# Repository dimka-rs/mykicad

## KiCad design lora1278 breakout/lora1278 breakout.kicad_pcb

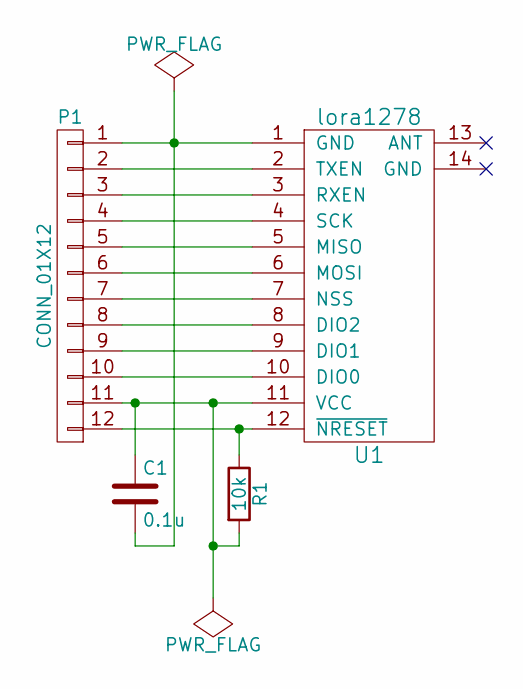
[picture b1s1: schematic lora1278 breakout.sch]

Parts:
C1: 0.1u; C_0805_HandSoldering
P1: CONN_01X12; Pin_Header_Straight_1x12
R1: 10k; R_0805_HandSoldering
U1: lora1278

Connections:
unnamed: C1.1, P1.11, R1.2, U1.11 (VCC)
unnamed: C1.2, P1.1, U1.1 (GND)
unnamed: P1.2, U1.2 (TXEN)
unnamed: P1.3, U1.3 (RXEN)
unnamed: P1.4, U1.4 (SCK)
unnamed: P1.5, U1.5 (MISO)
unnamed: P1.6, U1.6 (MOSI)
unnamed: P1.7, U1.7 (NSS)
unnamed: P1.8, U1.8 (DIO2)
unnamed: P1.9, U1.9 (DIO1)
unnamed: P1.10, U1.10 (DIO0)
unnamed: P1.12, R1.1, U1.12 (~NRESET)

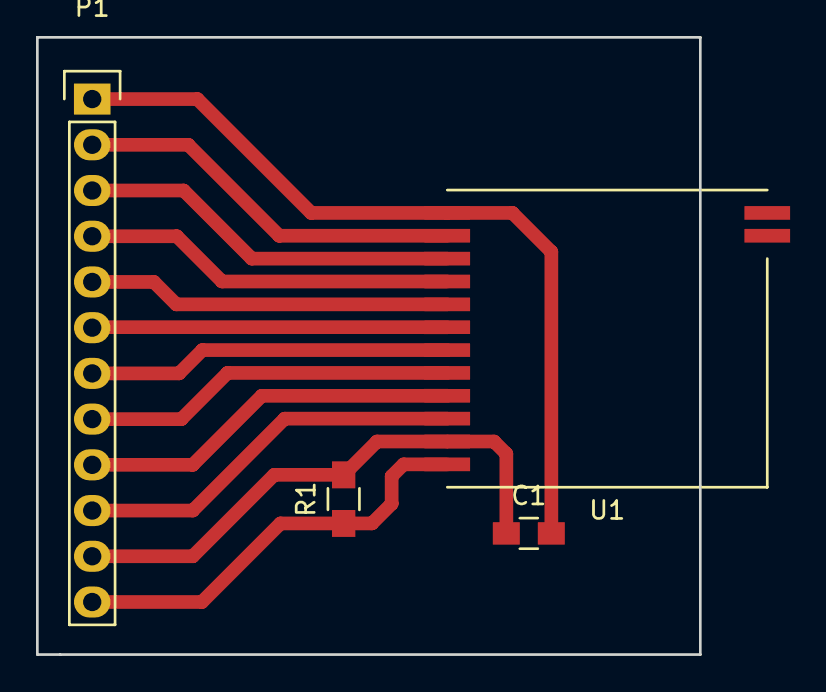
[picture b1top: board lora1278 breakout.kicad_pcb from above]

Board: 2 copper layers, 36.8 x 34.3 mm, 4 parts (0 on the bottom side), 12 nets.

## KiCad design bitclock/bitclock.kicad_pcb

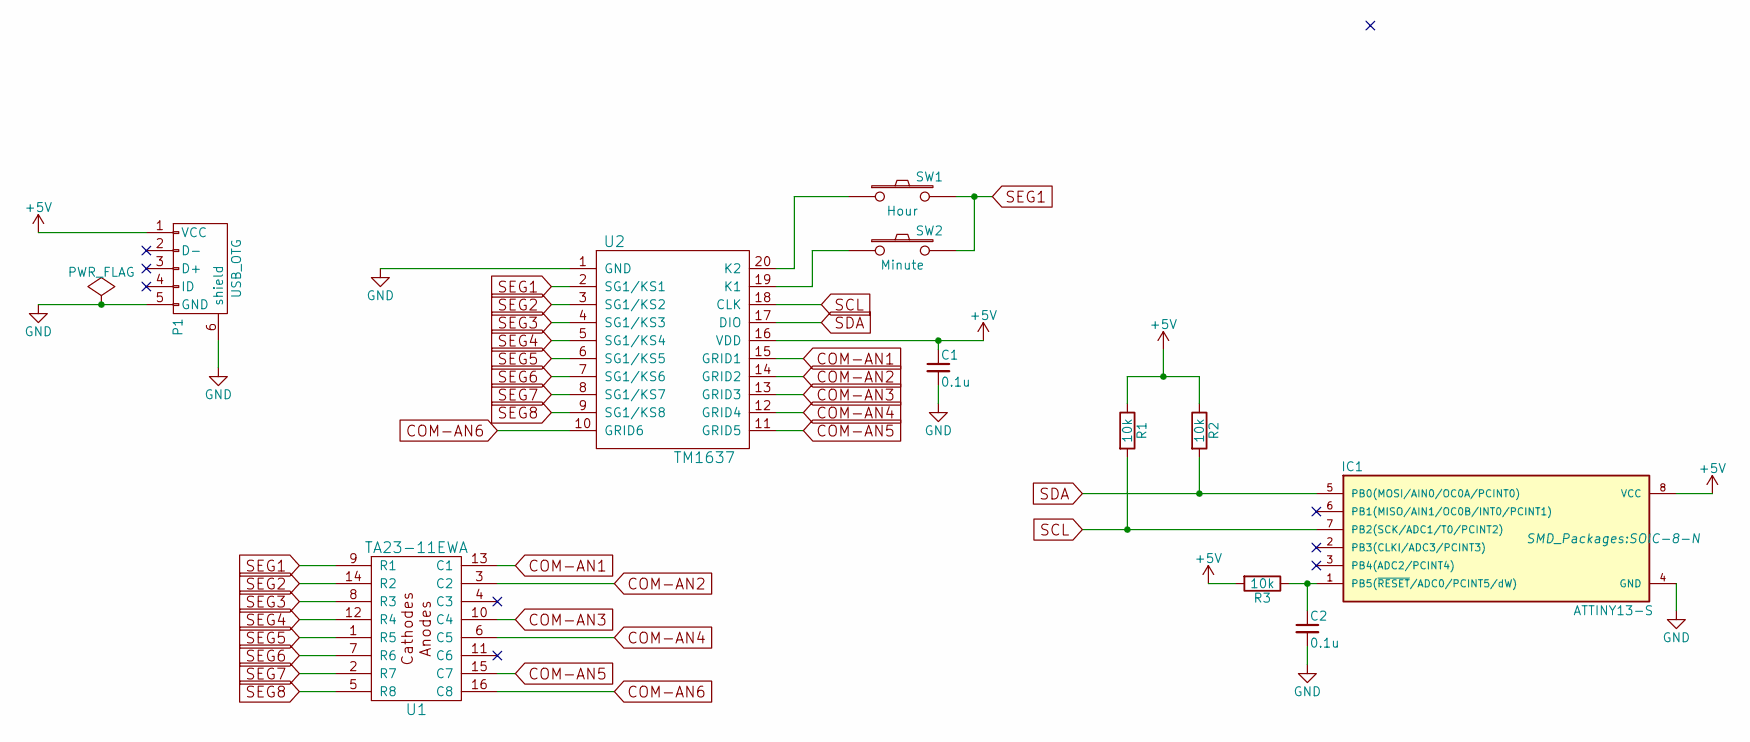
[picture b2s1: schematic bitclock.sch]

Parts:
C1, C2: 0.1u; C_0805_HandSoldering
IC1: ATTINY13-S; SOIC-8-N
P1: USB_OTG; USB_Mini-B
R1, R2, R3: 10k; R_0805_HandSoldering
SW1: Hour; SW_PUSH_SMALL
SW2: Minute; SW_PUSH_SMALL
U1: TA23-11EWA
U2: TM1637; SOIC-20_7.5x12.8mm_Pitch1.27mm

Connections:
+5V: C1.1, IC1.8 (VCC), P1.1 (VCC), R1.1, R2.1, R3.2, U2.16 (VDD)
COM-AN1: U1.13 (C1), U2.15 (GRID1)
COM-AN2: U1.3 (C2), U2.14 (GRID2)
COM-AN3: U1.10 (C4), U2.13 (GRID3)
COM-AN4: U1.6 (C5), U2.12 (GRID4)
COM-AN5: U1.15 (C7), U2.11 (GRID5)
COM-AN6: U1.16 (C8), U2.10 (GRID6)
GND: C1.2, C2.2, IC1.4 (GND), P1.5 (GND), P1.6 (shield), U2.1 (GND)
unnamed: C2.1, IC1.1 (PB5(~RESET~/ADC0/PCINT5/dW)), R3.1
unnamed: SW1.1, U2.20 (K2)
unnamed: SW2.1, U2.19 (K1)
SCL: IC1.7 (PB2(SCK/ADC1/T0/PCINT2)), R1.2, U2.18 (CLK)
SDA: IC1.5 (PB0(MOSI/AIN0/OC0A/PCINT0)), R2.2, U2.17 (DIO)
SEG1: SW1.2, SW2.2, U1.9 (R1), U2.2 (SG1/KS1)
SEG2: U1.14 (R2), U2.3 (SG1/KS2)
SEG3: U1.8 (R3), U2.4 (SG1/KS3)
SEG4: U1.12 (R4), U2.5 (SG1/KS4)
SEG5: U1.1 (R5), U2.6 (SG1/KS5)
SEG6: U1.7 (R6), U2.7 (SG1/KS6)
SEG7: U1.2 (R7), U2.8 (SG1/KS7)
SEG8: U1.5 (R8), U2.9 (SG1/KS8)

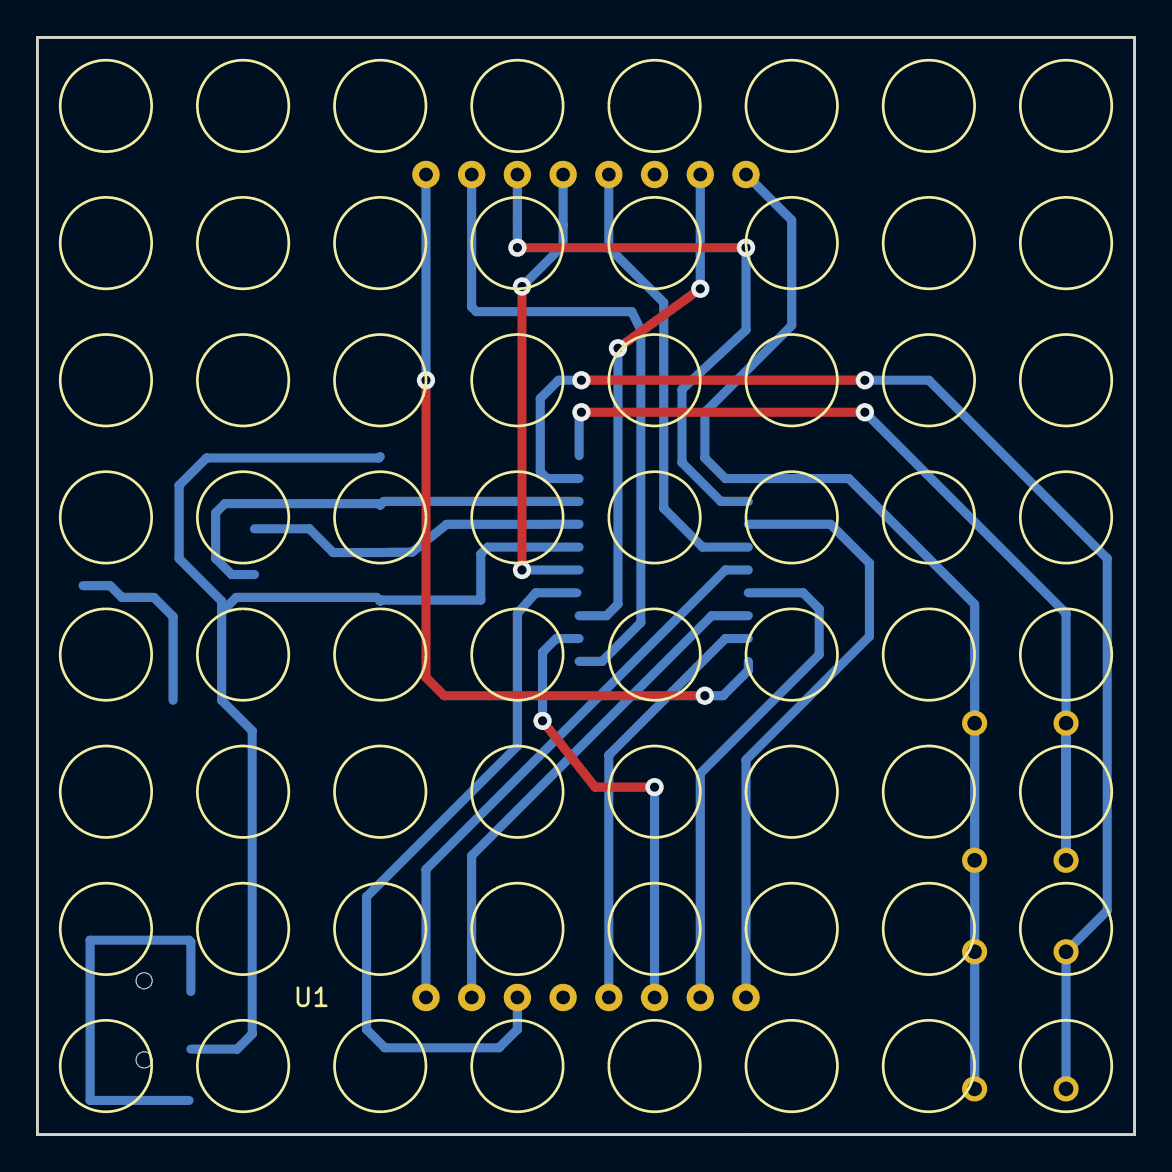
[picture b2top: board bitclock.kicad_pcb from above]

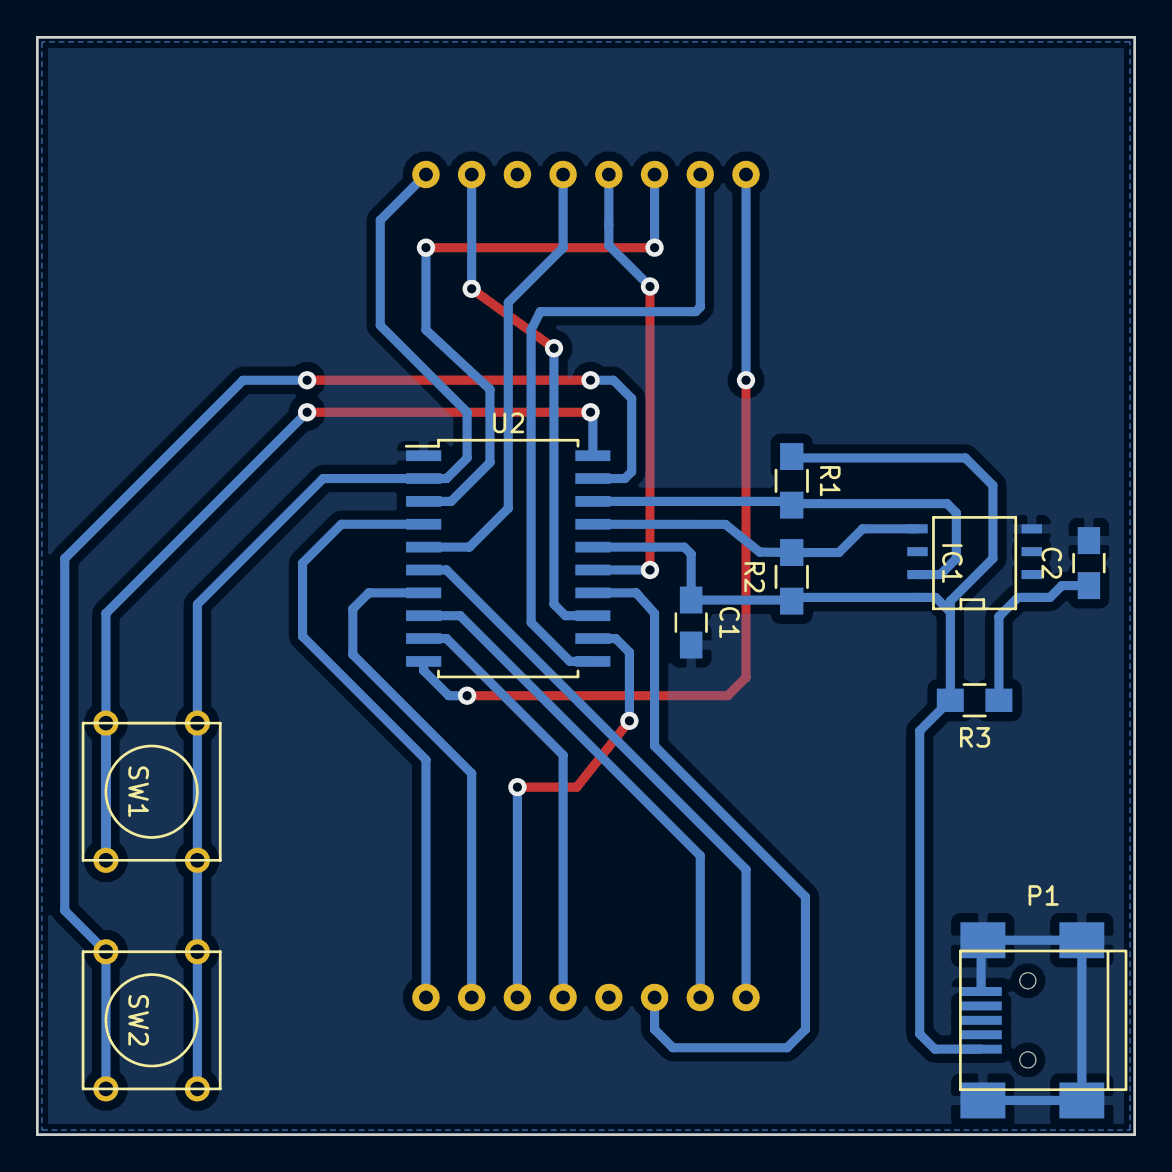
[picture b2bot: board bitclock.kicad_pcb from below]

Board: 2 copper layers, 61.0 x 61.0 mm, 11 parts (10 on the bottom side), 21 nets.

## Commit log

2016-07-21 added bitclock project
2016-07-21 bitclock: pcb trace started
2016-07-21 bitclock: done tracing pcb
2016-07-22 bitclock: pcb: wider traces, larger vias
2016-07-25 lora1278 breakout: added
2017-02-04 added iv9 clock
2017-11-04 uameter: start
2017-11-04 uameter: pcb rev1
